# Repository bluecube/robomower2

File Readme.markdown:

Autonomous outdoor robot, work in progress.

https://bluecube.github.io/robomower2

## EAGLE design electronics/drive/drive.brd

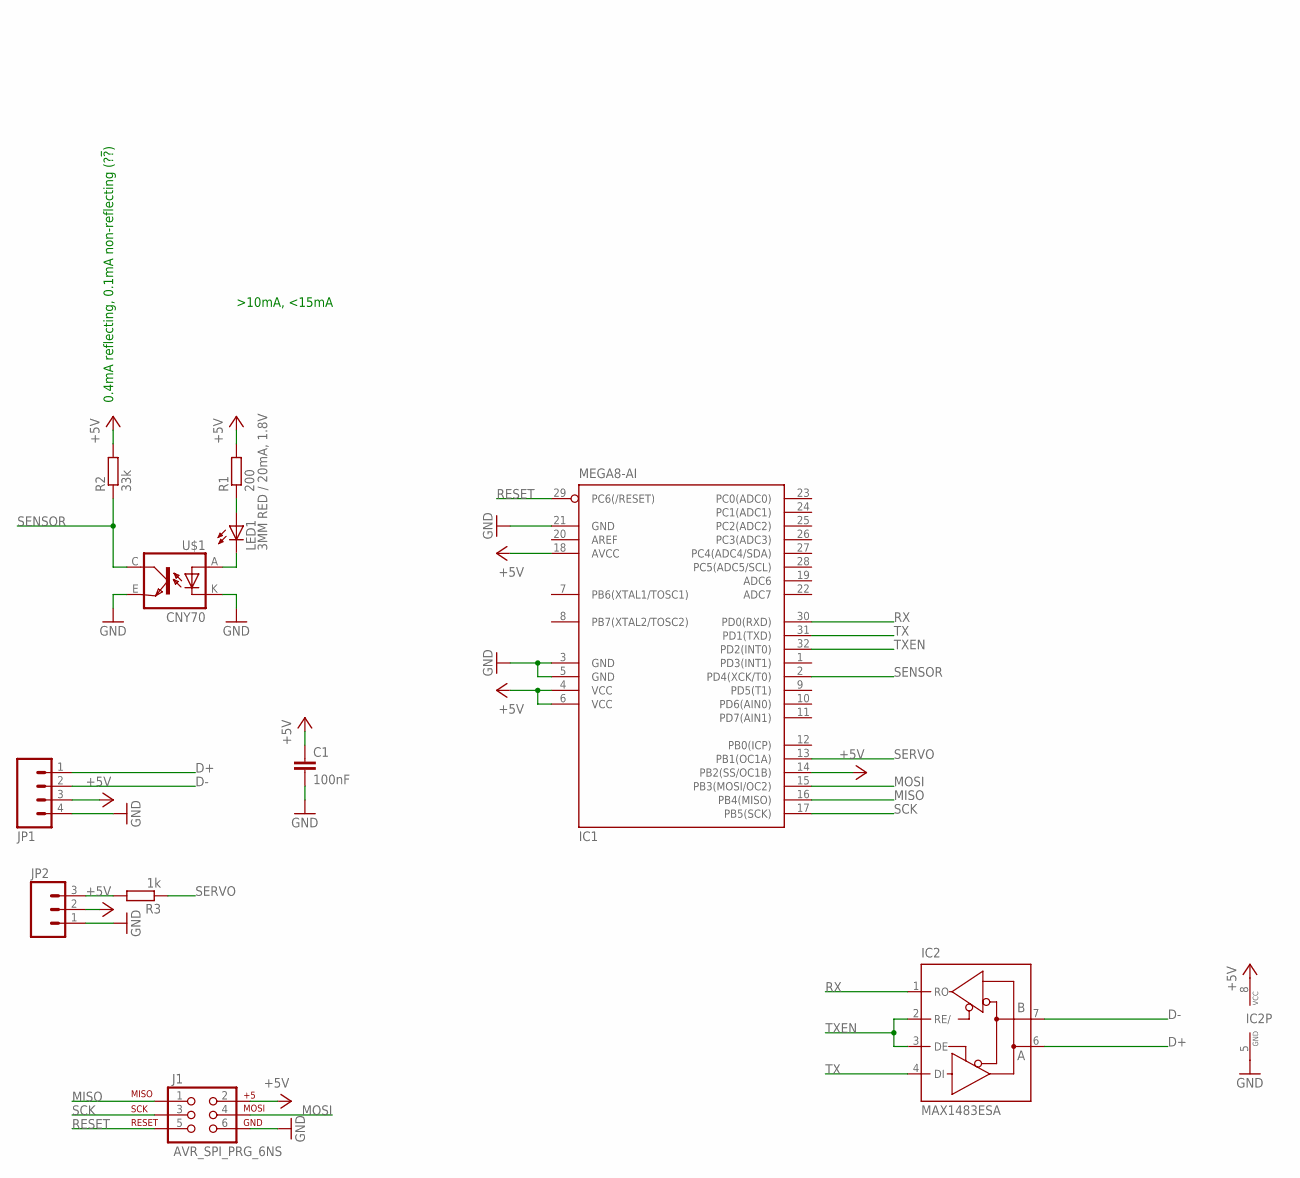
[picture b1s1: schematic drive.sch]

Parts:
C1: 100nF; C0805
IC1: MEGA8-AI; TQFP32-08
IC2: MAX1483ESA; SO08
J1: AVR_SPI_PRG_6NS; 2X3-NS
JP1: M04POLAR; MOLEX-1X4
JP2: M03PTH; 1X03
LED1: 3MM RED / 20mA, 1.8V; LED3MM
R1: 200; R0805
R2: 33k; R0805
R3: 1k; R0805
U$1: CNY70; 4

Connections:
+5V: C1.1, IC1.4 (VCC), IC1.6 (VCC), IC1.14 (PB2(SS/OC1B)), IC1.18 (AVCC), IC2.8 (VCC), J1.2, JP1.3, JP2.2, R1.2, R2.2
D+: IC2.6 (A), JP1.1
D-: IC2.7 (B), JP1.2
GND: C1.2, IC1.3 (GND), IC1.5 (GND), IC1.21 (GND), IC2.5 (GND), J1.6, JP1.4, JP2.1, U$1.E (EMI), U$1.K (C)
MISO: IC1.16 (PB4(MISO)), J1.1
MOSI: IC1.15 (PB3(MOSI/OC2)), J1.4
unnamed: JP2.3, R3.2
unnamed: LED1.K (C), U$1.A
unnamed: LED1.A, R1.1
RESET: IC1.29 (PC6(/RESET)), J1.5
RX: IC1.30 (PD0(RXD)), IC2.1 (RO)
SCK: IC1.17 (PB5(SCK)), J1.3
SENSOR: IC1.2 (PD4(XCK/T0)), R2.1, U$1.C (COL)
SERVO: IC1.13 (PB1(OC1A)), R3.1
TX: IC1.31 (PD1(TXD)), IC2.4 (DI)
TXEN: IC1.32 (PD2(INT0)), IC2.2 (RE/), IC2.3 (DE)

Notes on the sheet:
0.4mA reflecting, 0.1mA non-reflecting (?!?!)

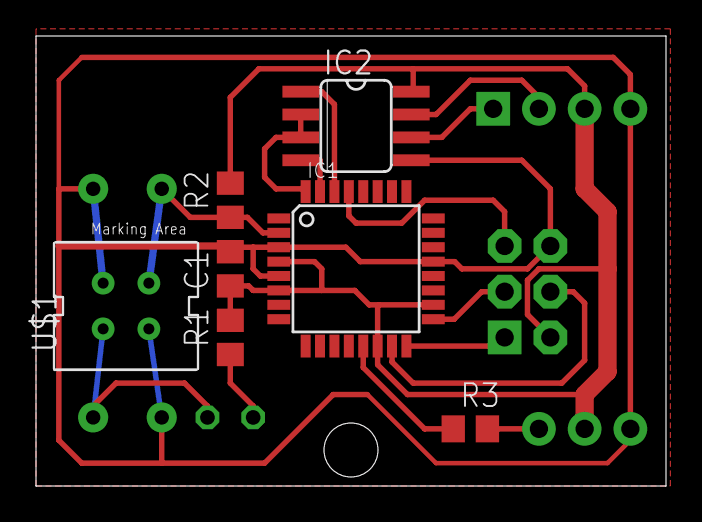
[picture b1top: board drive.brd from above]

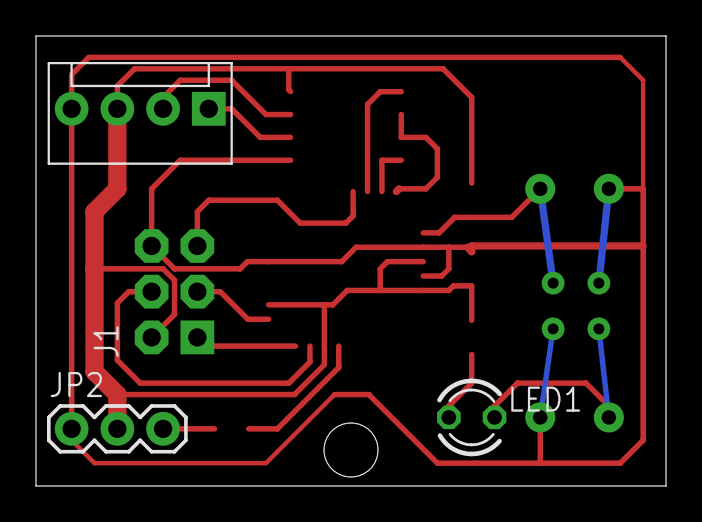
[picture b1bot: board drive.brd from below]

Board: 2 copper layers, 35.0 x 25.0 mm, 11 parts (4 on the bottom side), 16 nets.

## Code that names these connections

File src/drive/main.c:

#include <avr/io.h>
#include <avr/interrupt.h>
#include <stdint.h>
#include <robonet/robonet.h>

#if F_CPU != 8000000L
#error This will work only for 8MHz CPU frequency
#endif

#define SERVO_PRESCALER 8
#define SERVO_TICKS_PER_MS ((uint16_t)(F_CPU / (SERVO_PRESCALER * (uint16_t)1000)))
#define SERVO_NEUTRAL_POSITION ((3 * SERVO_TICKS_PER_MS) / 2)
#define SERVO_PERIOD (20 * SERVO_TICKS_PER_MS)

/// Calculate ((a << shift) / b) with correct rounding
/// a << (shift + 1) must fit into uint32_t
#define ROUNDED_DIVISION(a, b, shift) \
    (((((uint32_t)(a)) << ((shift) + 1)) / (b) + 1) >> 1)

uint16_t latchedTicks;

void motor_enable()
{
    PORTD |= _BV(PD4); // Enable sensor power

    TCNT1 = SERVO_PERIOD - 1; // We want a complete period of the servo to happen --
                              // including the first rising edge.

    TCCR1B |= _BV(CS10) | _BV(CS11);
        // setting the prescaler to 8 => enabling timer.
}

void motor_disable()
{
    TCCR1B &= ~(_BV(CS10) | _BV(CS11) | _BV(CS12));
        // Clear the prescaler flags => disable timer
    PORTB &= ~_BV(PB1); // Set the output pin to zero.

    PORTD &= ~_BV(PD4); // disable sensor power
}

/// Set the output value for the servo as signed integer from -127 to 127.
/// Value of -128 means disabling of the servo.
void servo_set(int8_t value)
{
    // OCR1A = SERVO_NEUTRAL_POSITION +
    //    (value * (SERVO_TICKS_PER_MS / 2)) / 127;
    uint16_t multiplier = ROUNDED_DIVISION(SERVO_TICKS_PER_MS / 2, INT8_MAX, 8);
    OCR1A = SERVO_NEUTRAL_POSITION + ((value * multiplier) >> 8);
}

/// Return the measured distance in ticks, or
/// UINT8_MAX to indicate overflow.
/// Also reset the counter and clear the overflow flag.
uint8_t distance_travelled()
{
    uint8_t tmp = TCNT0;
    TCNT0 = 0;

    if (TIFR & _BV(TOV0))
    {
        // If there was an overflow
        TIFR |= _BV(TOV0); // Clearing flag by writing 1 into it? Datasheet seems to say so.
        return UINT8_MAX;
    }
    else
    {
        return tmp;
    }
}

void init()
{
    // Output ports:
    DDRB |= _BV(PB1); // servo
    DDRD |= _BV(PD4); // sensor power

    // Timer0 (counting encoder pulses)
    TCCR0 |= _BV(CS02) | _BV(CS01) | _BV(CS00); // external clock source, rising

    // Timer1 (Generating servo PWM)
    TCCR1A =
        _BV(COM1A1) | // Clear OC1A on Compare Match, set OC1A at BOTTOM
        _BV(WGM11); // Fast PWM, counting to ICR1, ...
    TCCR1B =
        _BV(WGM12) | _BV(WGM13); // Fast PWM, counting to ICR1, continued
        // Timer disabled. The prescaler is set when servo output is enabled
    ICR1 = SERVO_PERIOD - 1; // setting the top value to 20ms

    robonet_init();
}

int main()
{
    init();
    sei(); // bzzzzzzzzz........

    while(true)
    {
        uint8_t status = robonet_receive();
        if (status == ROBONET_BUSY)
            continue;

        if (robonetBuffer.address == 0x0f)
        {
            // broadcast function 0x00: latch
            // TODO

            continue; // don't transmit anything
        }
        else if (robonetBuffer.address == 0x00 | ROBONET_OWN_ADDRESS)
        {
            // addressed function 0x00: order new speed and transmit latched value
            uint8_t orderedValue = robonetBuffer.data[0];

            *((uint16_t)robonetBuffer.data) = latchedTicks;
            robonetBuffer.length = 2;
        }

        // We're transmitting something, do the common stuff here
        robonetBuffer.address = 0x00;
        // TODO: Append the error status if it is nonzero
        robonet_transmit();
    }
}

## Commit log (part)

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2013-04-21 Initial commit, board for controling drive motors.
2013-04-21 Solid works sketch of motor board.
2013-04-21 Small fixes of drive board.
2013-04-21 Importing solidworks models.
2013-04-23 Started working on software for the driver board.
2013-04-25 Makefile for the driver board.
2013-04-28 Minor fixes and optimizations (all premature).
2013-04-28 Updated eagle gitignore.
2013-04-29 Division trick in motor driver code.
2013-04-29 Merging setup to main.
2013-05-01 Fix in driver code.
2013-05-06 Cleaning up the drive board.
2013-07-29 Updated motor driver board. Added ISP programming header, fixed problem with missing power to RS485.
2013-08-11 Returning the sensing resistor to the drive board.
2013-08-19 Untested implementation of the serial protocol.
2013-08-26 Simplifications of the robonet code and of macro arguments.
2013-08-26 First implementation of the master half of the robonet protocol. Again untested.
2013-08-27 Common makefile for avr.
2013-08-28 Lowering transmission speed.
2013-08-29 More drive board tweaking.
2013-08-29 WIP drive board software.
2013-09-09 MPCM and sync using the 9th bit.
2013-09-14 WIP servo signal generator and its test.
2013-09-22 Robonet doesn't need to be a package.
2013-09-23 Working servo test.
2013-09-24 Fiddling with the drive board.
2013-09-25 Link time optimizations.
2013-09-26 Fixed symlink
2013-09-30 Final modifications of the drive board.
2013-10-05 Editing the board based on the build experiences :-)
2013-10-23 Interface layer on top of robonet.
2013-10-27 Added missing symlink to servo library.
2013-10-27 Partially syncing software to the real board.
2013-10-27 Automatic message for enumerating devices.
2013-10-27 Basic version of the drive board software.
2013-11-09 Mentioning skipped automatic requests in the generated interface code.
2013-11-09 Emulating of link time optimization for AVR code.
2013-11-09 Removed the obsolete version file.
2013-11-09 -freorder-blocks generates a few (6) bytes larger and a tiny bit faster code. I like it :-)
2013-11-09 Minimal AVR program using the layer2 framework
2013-11-09 Cosmetic change.
2013-11-13 More verbose echo test.
2013-12-07 Changed how tick latching works.
2013-12-07 Adding PID parameters settings to drive interface.
2013-12-09 Premature optimizations.
2013-12-09 Indents in generated avr code.
2013-12-22 Force formatting of the binary name in common avr makefile.
2013-12-22 Makefile target for setting fuses on the avr.
2013-12-24 Additional buffer overrun check in the layer2 generated code.
2013-12-24 Longer echo test data.
2013-12-25 Changed the RoboNet protocol to 8 bit. It works now!
2013-12-26 Typo fix.
2013-12-26 Python proxies for the layer2 communication. Still missing is the actual packing and unpacking code for the variables in interfaces.
2013-12-26 Updating the board - More space for the programming connector - VCC connected to the programming connector - Removed the jumper wire
2013-12-26 Missing initialization of robonet status.
2013-12-26 Fixes.
2013-12-26 Robonet read timeouts.
2013-12-26 Todo list
2013-12-26 Fixing broadcast proxy.
2013-12-27 Updated value of the sensor resistor on a drive board.
2013-12-27 Fixing broadcast errors in the python code.
2013-12-27 Fix in layer2 proxy status checking.
2013-12-28 Updating measured values in the spreadsheet.
2013-12-28 Changed spelling in status message.
2013-12-28 WIP PI controller for drive board.
2013-12-30 Fixes in the direction change code and in PI controller.
2014-01-02 Slight optimization of drive code.
2014-01-02 Changed constant for directly controlling the servo to something more reasonable. (and matching to the comment).
2014-01-03 Drive board uses the full precision of servo output, all controller calculations are in simple 16bit integers.
2014-01-03 WIP drive test
2014-01-03 robonet uses logging instead of prints.
2014-01-03 Uncommenting joystick code, formatting.
2014-01-03 Removed integrator limit from the interface.
2014-01-03 Safety stop after 1 second without speed command for drive board.
2014-01-03 Formating changes in drive board test.
2014-01-03 Safe stop of drive motor, little refactoring.
2014-01-03 Servo preprocessing now internally uses floats for more flexibility.
2014-01-03 Updated measured numbers in the spreadsheet.
2014-01-05 Updated comment.
2014-01-18 Python 2 compatibility (because of pyfltk).
2014-01-18 Some logging in layer2 proxy.
2014-01-19 Revert "Dial fltk widget. Just for fun."
    This reverts commit 39a5aa8a5c6487695792f36788e948a83ed60dbb.
2014-01-20 Robot configuration in a file.
2014-01-20 Extending the XY widget.
2014-01-20 positive Y is forward
2014-01-20 Removed obsolete __future__ thingie
2014-01-20 Fix in loop timing.
2014-01-25 Updated todo notes.
2014-01-26 Correctly raise an exception when attempting to load nonexistent interface.
2014-01-26 Constants in the interface files, servo (and PID) period is controlled by the interface parameter.
2014-01-26 Removed check for maximal packet size from robonet. This is checked one layer higher.
2014-01-31 Playing with a map widget.
2014-01-31 Joystick in gui.
2014-02-01 Configurable port settings.
2014-02-02 Fixed a bug in Makefile dependencies with the whole program target.
2014-02-02 Working calibration code for turningy ESC.
2014-02-02 Smoother joystick control around the zero speeds.
2014-02-02 Joystick nonlinearity in config file.
2014-02-02 Renaming constants.
2014-02-02 Use fake hardware if the real one cannot be found.
2014-02-02 Updated dimensions
2014-02-03 Changed drive model. Now it should be asymptotically correct for circular paths with the angle turned approaching 0.
2014-02-03 Todo notes.
2014-02-03 Very simple square following code without any feedback.
2014-02-15 Refactoring the main program to use a generic controller + fixing sign of turns.
2014-02-15 Fixes in joystick signs.
2014-02-15 Widgets.
2014-02-15 Renaming content of the gui package.
2014-02-17 Fixes in the pattern driving code.
2014-02-17 Very basic data logger -- preparations for the drive calibration.
2014-02-17 Time differences in recording.
2014-02-17 Larger joystick nonlinearity to better control the robot at low sppeds.
2014-02-17 Logging requests as well as velocities.
2014-03-31 Fix embarassingly simple bug in drive board software.
2014-03-31 Use fixed point arithmetic for PID controller constants + guessed values.
2014-04-18 PID constants slider in gui.
2014-04-18 Slider nonlinearity.
2014-04-19 Removed obsolete timer.
2014-04-20 Moved the programming connector on drive board.
    Now all three connectors can be connectors can be in at the same time.
2014-04-22 Separate resolution for left and right wheel.
2014-04-22 Starting the drive calibration code.
2014-04-26 Drawing lines in map widget.
2014-04-27 Schematics for the 12V part of the robot electronics.
2014-04-27 Differential drive model now returns new sample instead of modifying it.
    Calibration seems to work, although I have no idea why.
2014-05-18 Map widget changes sample indicator size depending on sample count.
2014-05-26 Preparing calibration code for stdev estimation.
2014-06-01 Fixed error in calibration distance to line segment code.
2014-06-15 Gui logging widget
2014-06-16 Starting implementation of Frechet distances,
    passing test for the decision version, failing test for the value version.
2014-06-17 Almost working Frechet distance.
    Just a bit is missing :-)
2014-06-23 Implemented the last part for frechet distances.
2014-06-25 Not functional calibration code.
2014-06-27 Removed obsolete comment.
2014-06-27 Untested initial commit.
2014-06-27 Readme file. I hope that the url is correct.
2014-06-28 Fixes in gui.
2014-06-28 Logging when changing PID settings.
2014-06-28 Enabling velocity in the gui again.
2014-06-28 Motor RPM meters for gui.
2014-06-29 Create LICENCE
2014-06-29 Update LICENCE
2014-06-30 Mechanics page.
2014-06-30 TODO list.
2014-06-30 Proper rounding in serialised values in layer2.
2014-06-30 Increased drive motor PID frequency to 100Hz, decreased derivative parameter for PID.
2014-06-30 Todo notes will be on the pages.
2014-06-30 Fixed wrong index in the calibration code.
2014-06-30 Rough gui showing calibration progress.
2014-06-30 Comment for drawing the calibration ground truth in main.
2014-06-30 Back to Hausdorff distance for calibration.
2014-06-30 Another simulated calibration data, this time driving around the track twice.
2014-06-30 Minor changes in the calibration code.
2014-07-03 Calculating max motor torque in the spreadsheet.
2014-07-03 Experimental smoothing of error derivation in drive PID.
2014-07-05 Max width for images.
2014-07-06 CSS, B*TCHES!
2014-07-09 Fixed typo in drive board firmware.
2014-07-09 Doubling drive board sampling rate by using a tiny bit of software trickery
    Or maybe by just extending the existing trickery....
    Untested.
2014-07-11 Fixed image titles in the mechhanics page.
2014-07-11 Fix in the couter extension trick for drive board firmware.
2014-07-11 8 bit integers for avr code. Compacts the output a bit.
2014-07-12 Fixed value mising from the 8 tick to 16 tick conversion.
2014-07-12 New PID params + more smoothing.
2014-07-13 Moved the path to robonet header from the interface file to generator parameters.
2014-07-13 More PID tuning, fixed a bug with the 8 bit integers compiler flag.
2014-07-14 Tweaking the mechanics page.
2014-07-14 Motor control page.
2014-07-14 Internal communication page.
2014-07-31 MathJax in the default layout.
2014-07-31 script to run a local jekyll instance.
2014-08-01 Updated internal communication page.
2014-08-01 Simulated testing data for calibration
2014-08-24 Added images.
2014-08-30 Updated todo list.
2014-08-30 Added motion model and stub of calibration.
2014-09-17 Another iteration of local path planner.
2014-09-18 Local path planner notes.
2014-09-21 Fixed path length calculation in the local planner.
2014-09-23 Minor changes in local planner.
2014-09-27 Path iterators for local planner.
2014-09-28 Untested path iterator that concatenates local paths.
2014-10-12 Removed angular acceleration from config file.
2014-10-12 Stub of local planner test.
2014-10-12 Fix in path planning package.
2014-10-13 Minor cleanup in the servo library includes.
2014-10-17 Base class for path iterator.
2014-10-25 Changed the top level loop for the path planner experiment.
2014-10-25 Completely untested KdTree in PRM.
2014-10-27 Pretty printing Kd-trees.
2014-10-27 Test of Kd-tree and fixes.
2014-10-28 More general line drawing in map widget.
2014-10-28 Removed debug prints.
2014-10-28 Fixed local planner test and local planner.
2014-10-28 Halton sequences for generating random nodes.
2014-10-29 Different connection strategy for prm. Doesn't help.
2014-10-29 Drunk path planning..
2014-10-29 Started redoing the paht planner page.
2014-11-02 New strategy for adding nodes to roadmap.
2014-11-03 Playing with path smoothing.
2014-11-07 Minor modifications for tests.
2014-11-07 Changed end of path behavior of path iterators.
    Now they stay at the end point instead of raising StopIteration.
2014-11-07 Refactoring in local planner test.
2014-11-07 Fixed wrong velocity polynomial in local planner.
2014-11-07 Proper detection of finished path iterator.
2014-11-10 Checking the values of halton sequence.
2014-11-10 Not adding nodes to roadmap if a close enough neighbor is already there.
2014-11-11 Saving the roadmap between runs
    + moved gitignore file
2014-11-11 More samples in the roadmap.
2014-11-13 Path smooting tweaks.
2014-11-13 Using state cost when selecting candidate nodes for connecting to roadmap.
2014-11-23 First version of a controller for automatic driving.
2014-12-23 Fixed one bug in local path iterator.
2014-12-23 Test refactoring.
2014-12-26 Explicitly recalculating travel time when returning path from prm.
2014-12-26 Display intended robot position in the gui.
2014-12-28 Path following.
2014-12-29 Someone wants a blog from this site, right?
2014-12-29 Change wording in the atom feed paragraph.
2015-01-03 Basic remote gui using xmlrpc.
2015-01-16 Updated motor control page.
